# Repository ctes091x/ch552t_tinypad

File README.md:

# CH552TinyPad

6 key macropad with USB microcontroller CH552T

## bill of materials

- R1: 330
- R2: 10k
- R3, R4: 5.1k
- C1, C2: 0.1uF
- U1: CH552T
- J1: PinHeader 2x10
- J2: USB-C receptacle
- U1: CH552T
- SW1~SW6: CherryMX compatible keyswitch
- SW7: SMD tactile switch

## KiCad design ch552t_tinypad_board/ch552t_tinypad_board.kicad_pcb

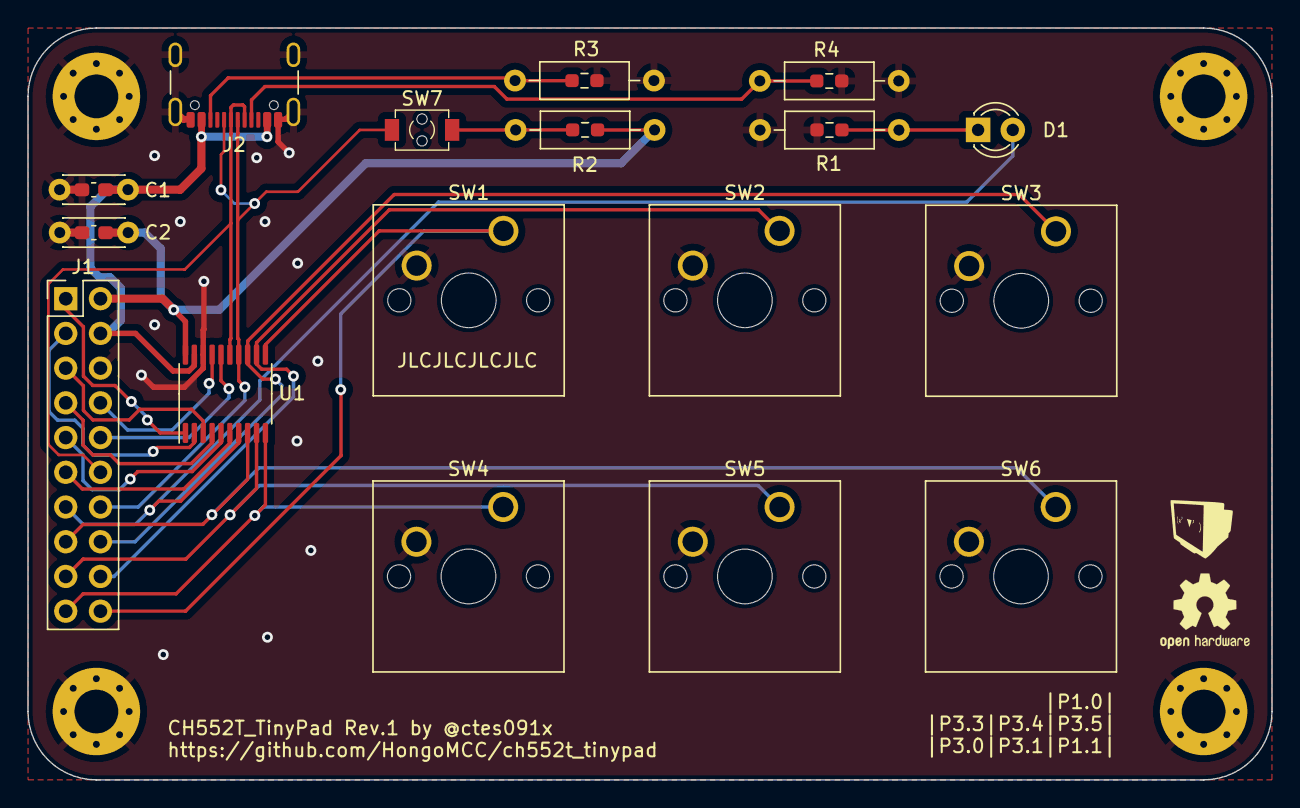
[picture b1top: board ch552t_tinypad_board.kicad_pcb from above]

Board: 2 copper layers, 91.0 x 55.0 mm, 21 parts (0 on the bottom side), 24 nets.

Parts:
C1, C2: 0.1u; C_SMD_0603_1608_Disc_DualUse
D1: LED; LED_D3.0mm
H1, H2, H3, H4: MountingHole_Pad; MountingHole_3.2mm_M3_Pad_Via
J1: Conn_02x10_Odd_Even; PinHeader_2x10_P2.54mm_Vertical
J2: USB_C_Receptacle_USB2.0; USB_C_Receptacle_GCT_USB4105-xx-A_16P_TopMnt_Horizontal
R1, R2: 10k; R_SMD_0603_1608_THT_DIN0207_DualUse
R3, R4: 5.1k; R_SMD_0603_1608_THT_DIN0207_DualUse
SW1, SW2, SW3, SW4, SW5, SW6: SW_Push; SW_Cherry_MX_1.00u_PCB
SW7: SW_Push; SW_SPST_TVAF06_A020B_R
U1: CH552T; TSSOP-20_4.4x6.5mm_P0.65mm

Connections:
/3V3: C2.1, J1.2, R2.1, U1.20 (3V3)
/D+: J1.14, J2.A6 (D+), J2.B6 (D+), SW7.1, U1.14 (P3.6/UDP)
/D-: J1.12, J2.A7 (D-), J2.B7 (D-), U1.15 (P3.7/UDM)
/P1.0: D1.2 (A), J1.13, U1.7 (P1.0/T2/CAP1/TIN0)
/P1.1: J1.15, SW6.1, U1.8 (P1.1/T2EX/CAP2/TIN1/VBUS2/AIN0)
/P1.2: J1.8, U1.17 (P1.2/XI/RXD__)
/P1.3: J1.10, U1.16 (P1.3/XO/TXD__)
/P1.4: J1.3, U1.2 (P1.4/T2_/CAP1_/SCS/TIN2/UCC1/AIN1)
/P1.5: J1.5, U1.3 (P1.5/MOSI/PWM1/TIN3/UCC2/AIN2_)
/P1.6: J1.7, U1.4 (P1.6/MISO/RXD1/TIN4_)
/P1.7: J1.9, U1.5 (P1.7/SCK/TXD1/TIN5)
/P3.0: J1.19, SW4.1, U1.10 (P3.0/PWM1_/RXD)
/P3.1: J1.17, SW5.1, U1.9 (P3.1/PWM2_/TXD_)
/P3.2: J1.1, U1.1 (P3.2/TXD1_/INT0/VBUS1/AIN3)
/P3.3: J1.20, SW1.1, U1.11 (P3.3/INT1)
/P3.4: J1.18, SW2.1, U1.12 (P3.4/PWM2/RXD1_/T0)
/P3.5: J1.16, SW3.1, U1.13 (P3.5/T1)
/reset: J1.11, U1.6 (RST/T2EX_/CAP2__)
GND: C1.2, C2.2, H1.1, H2.1, H3.1, H4.1, J1.6, J2.A1 (GND), J2.A12 (GND), J2.S1 (SHIELD), R1.2, R3.2, R4.2, SW1.2, SW2.2, SW3.2, SW4.2, SW5.2, SW6.2, U1.18 (GND/VSS)
unnamed: D1.1 (K), R1.1
unnamed: J2.A5 (CC1), R4.1
unnamed: J2.B5 (CC2), R3.1
unnamed: R2.2, SW7.2
VCC: C1.1, J1.4, J2.A4 (VBUS), J2.A9 (VBUS), U1.19 (VCC/VDD)

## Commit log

2023-12-22 chore: drag and drop sample codes
    from HidKeyboard.ino
2024-01-03 feat: create circuit board
    表面に全部品を配置
    mcuの全ピンを引き出すピンヘッダへの配線で詰みそう
2024-02-01 feat: Create some footprints
2024-02-01 feat: auto wiring and board outline
2024-02-05 fix: hole position of tactile switch footprint
2024-02-05 feat: connect keys to MCU
2024-02-14 fix: pulldown CC pins on USB-C
2024-02-14 feat: Create mcc_logo silkscreen footprint
2024-02-17 feat: Create some logo footprint
2024-02-17 feat: silkscreen artwork(?)
2024-02-18 feat: add revision number on silkscreen
2024-02-23 feat: straighten diff pair of USB
2024-02-23 hotfix: replace swapped USB differential pair
    pcb is not fixed
2024-02-24 fix: rewire USB diff pair
2024-02-24 chore: Generate gerber file
2024-04-15 feat: Create ch552t_tinypad_sketch.ino
2024-04-15 doc: Update README.md
